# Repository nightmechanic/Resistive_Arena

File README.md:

Resistive_Arena
===============

Standard resistors board

This is a small project for a board with a few relatively accurate resitors with (relatively...) low temperature coeficients.
The purpose is to allow performance checking and possible calibration of Multimeters (not high accuracy ones, of course).

The project was budget limited, so I collected teh best value for money resistors I could find, resulting in some SMT resistors and a couple of, different, through-hole resistors.

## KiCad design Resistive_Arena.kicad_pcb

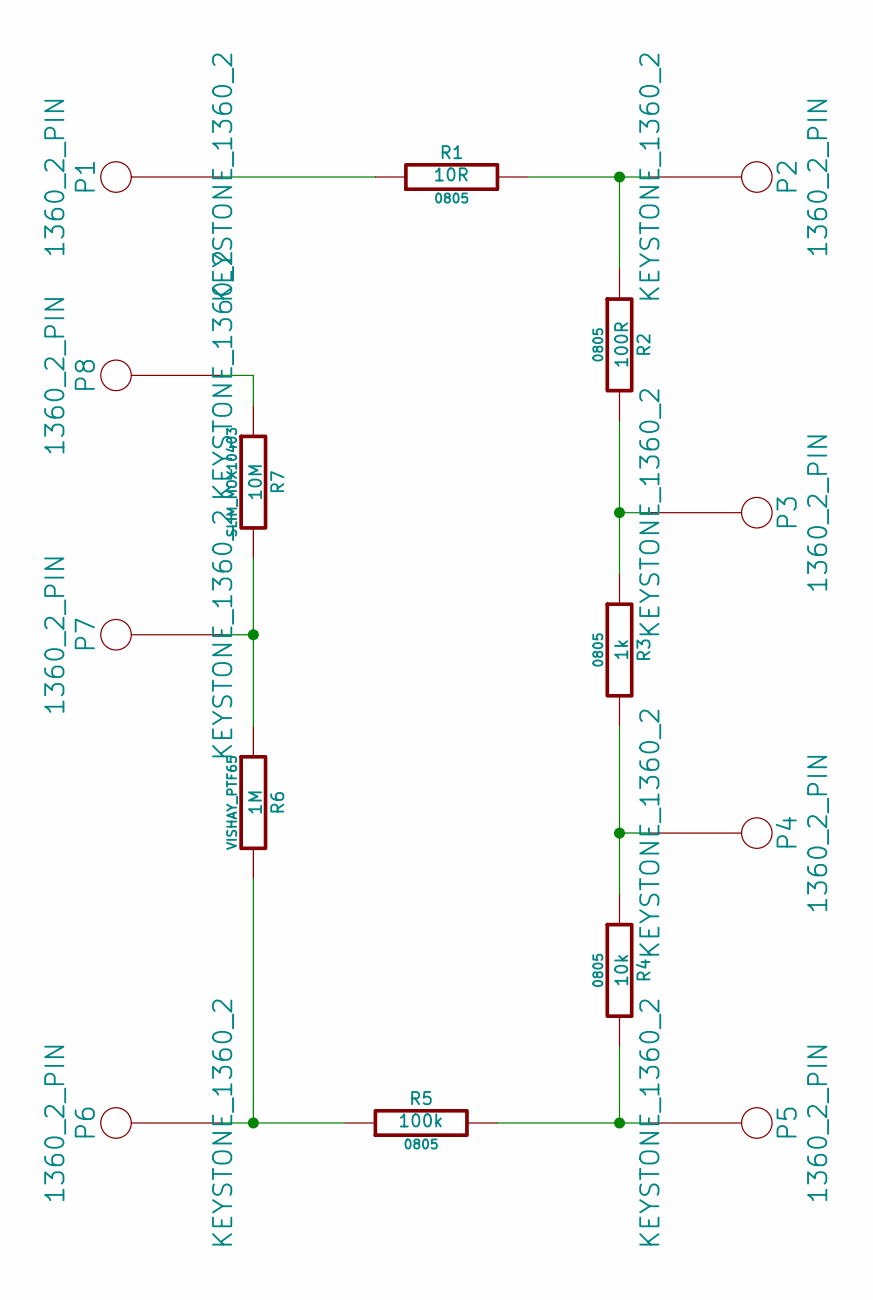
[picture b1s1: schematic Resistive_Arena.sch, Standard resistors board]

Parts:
P1, P2, P3, P4, P5, P6, P7, P8: 1360_2_PIN; KEYSTONE_1360_2
R1: 10R; 0805
R2: 100R; 0805
R3: 1k; 0805
R4: 10k; 0805
R5: 100k; 0805
R6: 1M; VISHAY_PTF65
R7: 10M; SLIM_MOX10403

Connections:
unnamed: P1.1, R1.1
unnamed: P2.1, R1.2, R2.1
unnamed: P3.1, R2.2, R3.1
unnamed: P4.1, R3.2, R4.1
unnamed: P5.1, R4.2, R5.2
unnamed: P6.1, R5.1, R6.2
unnamed: P7.1, R6.1, R7.2
unnamed: P8.1, R7.1

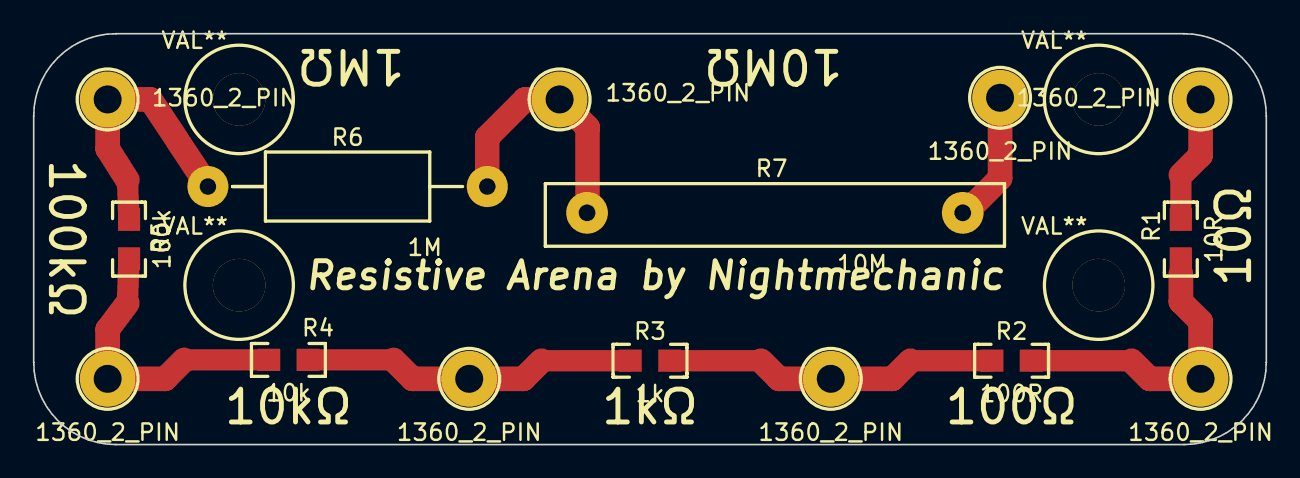
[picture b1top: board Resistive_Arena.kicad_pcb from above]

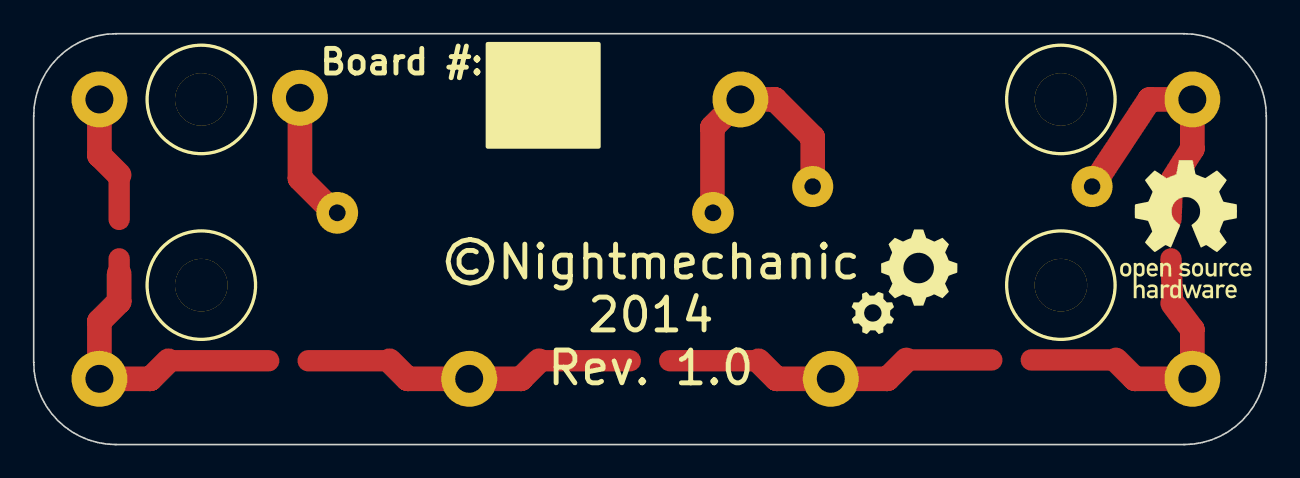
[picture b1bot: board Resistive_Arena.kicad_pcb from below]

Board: 2 copper layers, 75.0 x 25.0 mm, 21 parts (2 on the bottom side), 8 nets.

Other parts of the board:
Mechanical_M3, Mechanical_M3#2, Mechanical_M3#3, Mechanical_M3#4: VAL**; Mechanical_M3
VAL: REF; OSHW_F.SilkS_8mm_flipped
VAL#2: REF; Gears_F.SilkS_8mm_flipped

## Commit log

2014-05-22 Version 1.0
    First version
2014-06-06 Added models for 3D pcb view

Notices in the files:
Resistive_Arena.kicad_pcb:
©Nightmechanic
